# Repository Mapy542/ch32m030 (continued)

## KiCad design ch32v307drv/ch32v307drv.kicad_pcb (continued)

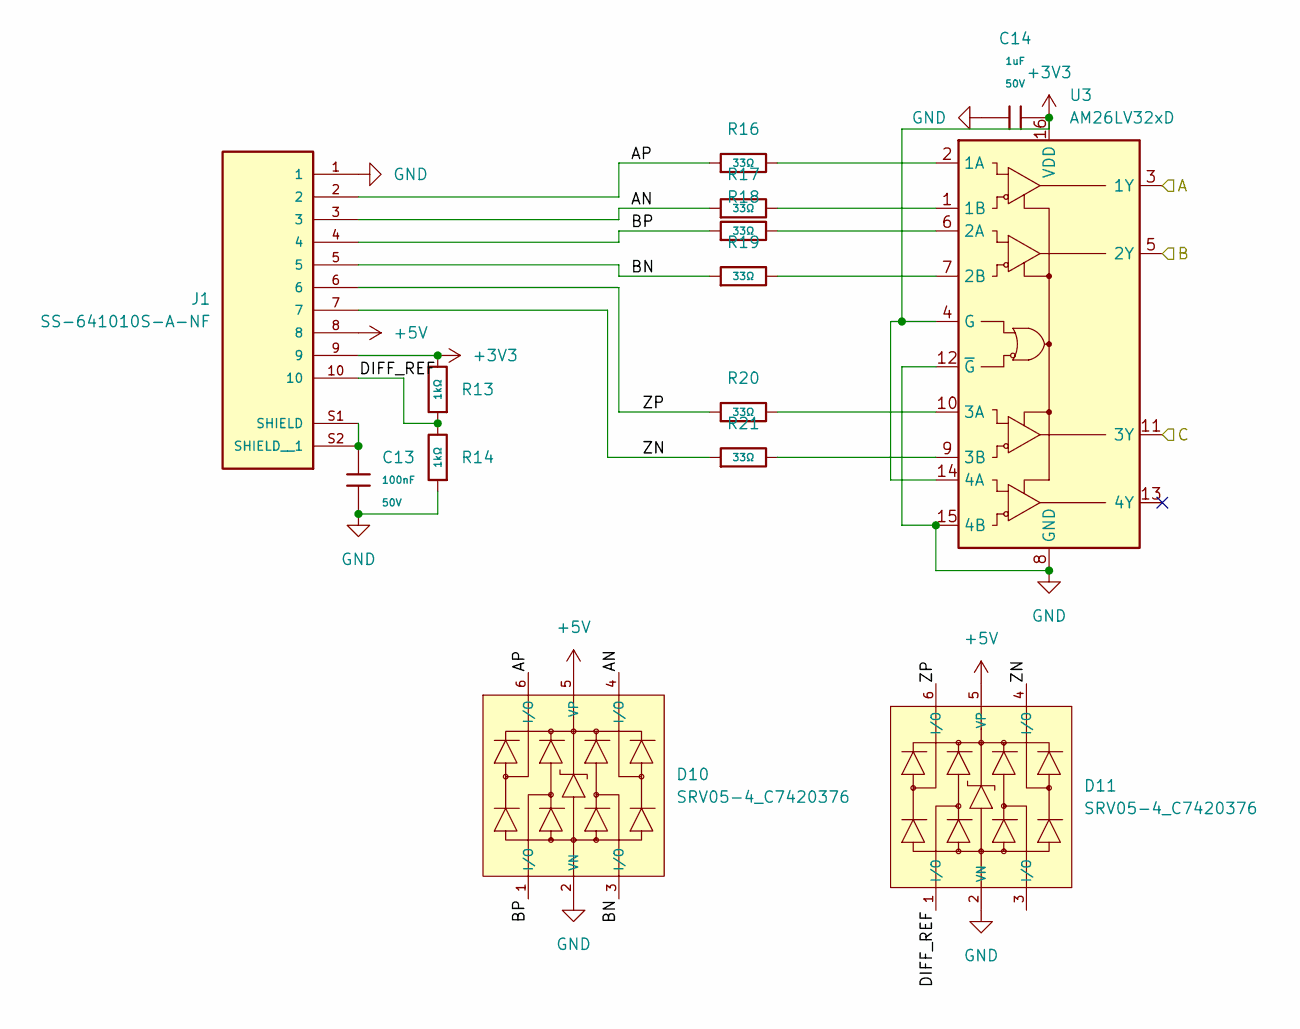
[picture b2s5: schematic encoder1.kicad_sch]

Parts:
C13: 100nF; C_1206; Voltage Rated 50V; Tolerance ±10%; Part CL31B104KBCNNNC; LCSC C24497
C14: 1uF; C_0603; Voltage Rated 50V; Tolerance ±10%; Part CL10A105KB8NNNC; LCSC C15849
D10, D11: SRV05-4_C7420376; SOT-23-6_L2.9-W1.6-P0.95-LS2.8-BL-1; Breakdown Voltage (Vbr) 6V; Clamping Voltage@Ipp 12.5V; Part SRV05-4; LCSC C7420376
J1: SS-641010S-A-NF; BEL_SS-641010S-A-NF; PARTREV A11
R13, R14: 1kΩ; R_0603; Overload Voltage (Max) 75V; Tolerance ±1%; Part 0603WAF1001T5E; LCSC C21190
R16, R17, R18, R19, R20, R21: 33Ω; R_0603; Overload Voltage (Max) 75V; Tolerance ±1%; Part 0603WAF330JT5E; LCSC C23140
U3: AM26LV32xD; SOIC-16_3.9x9.9mm_P1.27mm

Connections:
+3V3: C14.2, J1.9, R13.2, U3.4 (G), U3.14 (4A), U3.16 (VDD); also elsewhere on the board
+5V: D10.5 (VP), D11.5 (VP), J1.8; also elsewhere on the board
/ENC0_A: U3.3 (1Y); also elsewhere on the board
/ENC0_B: U3.5 (2Y); also elsewhere on the board
/ENC0_C: U3.11 (3Y); also elsewhere on the board
/encoder1/AN: D10.4 (I/O), J1.3, R17.1
/encoder1/AP: D10.6 (I/O), J1.2, R16.1
/encoder1/BN: D10.3 (I/O), J1.5, R19.1
/encoder1/BP: D10.1 (I/O), J1.4, R18.1
/encoder1/DIFF_REF: D11.1 (I/O), J1.10, R13.1, R14.2
/encoder1/ZN: D11.4 (I/O), J1.7, R21.1
/encoder1/ZP: D11.6 (I/O), J1.6, R20.1
GND: C13.2, C14.1, D10.2 (VN), D11.2 (VN), J1.1, R14.1, U3.8 (GND), U3.12 (~G), U3.15 (4B); also elsewhere on the board
unnamed: C13.1, J1.S1 (SHIELD), J1.S2 (SHIELD__1)
unnamed: R16.2, U3.2 (1A)
unnamed: R17.2, U3.1 (1B)
unnamed: R18.2, U3.6 (2A)
unnamed: R19.2, U3.7 (2B)
unnamed: R20.2, U3.10 (3A)
unnamed: R21.2, U3.9 (3B)

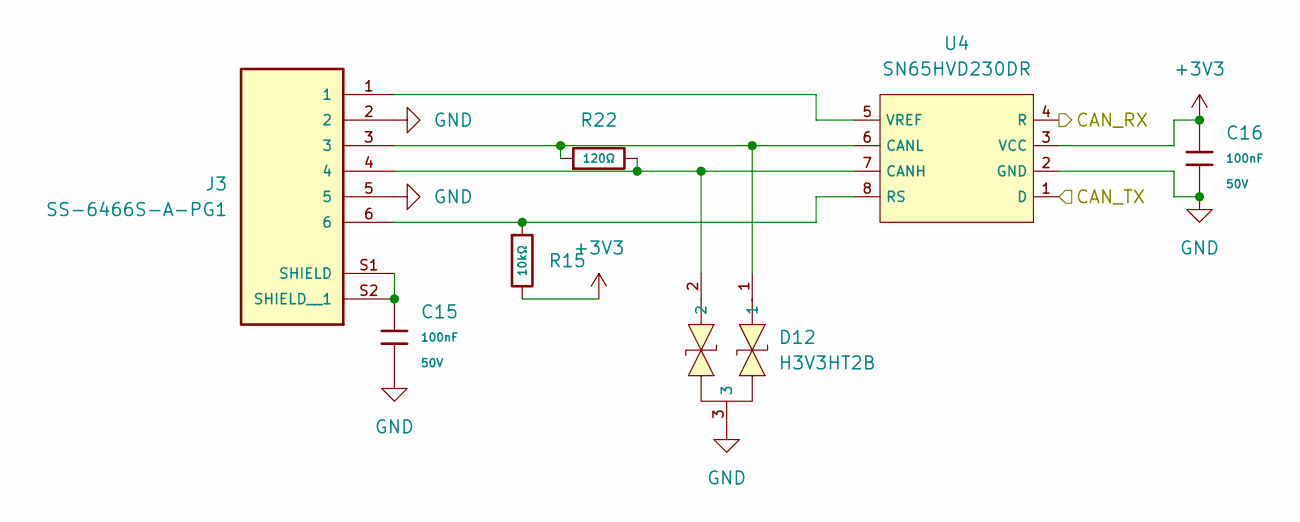
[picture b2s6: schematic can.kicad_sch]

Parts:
C15: 100nF; C_1206; Voltage Rated 50V; Tolerance ±10%; Part CL31B104KBCNNNC; LCSC C24497
C16: 100nF; C_0603; Voltage Rated 50V; Tolerance ±10%; Part CC0603KRX7R9BB104; LCSC C14663
D12: H3V3HT2B; SOT-23-3_L2.9-W1.3-P1.90-LS2.4-BR; Part H3V3HT2B; LCSC C20617923
J3: SS-6466S-A-PG1; BEL_SS-6466S-A-PG1; PARTREV A5
R15: 10kΩ; R_0603; Overload Voltage (Max) 75V; Tolerance ±1%; Part 0603WAF1002T5E; LCSC C25804
R22: 120Ω; R_0603; Overload Voltage (Max) 75V; Tolerance ±1%; Part 0603WAF1200T5E; LCSC C22787
U4: SN65HVD230DR; SOIC-8_L4.9-W3.9-P1.27-LS6.0-BL; Supply Voltage 3V~3.6V; Part SN65HVD230DR; LCSC C12084

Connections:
+3V3: C16.2, R15.2, U4.3 (VCC); also elsewhere on the board
/CAN_RX: U4.4 (R); also elsewhere on the board
/CAN_TX: U4.1 (D); also elsewhere on the board
GND: C15.2, C16.1, D12.3, J3.2, J3.5, U4.2 (GND); also elsewhere on the board
unnamed: C15.1, J3.S1 (SHIELD), J3.S2 (SHIELD__1)
unnamed: D12.2, J3.4, R22.2, U4.7 (CANH)
unnamed: D12.1, J3.3, R22.1, U4.6 (CANL)
unnamed: J3.6, R15.1, U4.8 (RS)
unnamed: J3.1, U4.5 (VREF)

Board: 4 copper layers, 177 parts (4 on the bottom side), 132 nets, no tracks yet.

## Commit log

2026-04-23 ch32m030 card board
2026-04-24 update board
2026-05-05 add ch32v307drv
2026-05-08 more design
2026-05-08 back
2026-06-03 update to share
2026-06-03 add context
2026-06-04 add rs-422 termination resistors
2026-06-12 update cpb
